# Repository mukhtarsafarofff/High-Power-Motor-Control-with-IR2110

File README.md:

(ENG) The IR2110 is a popular h-bridge half driver. It is designed to drive high voltage MOSFET and IGBT circuits. It does this without the use of p-channel MOSFETs or photovoltaic opto-couplers. The circuit generates HIGH side MOSFET gate voltage from a diode, bootstrap capacitor combination. The IR2110 is an 14-pin DIP IC and I used 2 for a complete h-bridge. The schematic to each half is identical. I used the 15V MOSFET/IGBT gate voltage with a 5-volt regular to supply the digital voltage (VDD) of 5V. The motor power supply is separate and is limited by the MOSFETs used and motor voltage up to 500-volts.  IR2110 illustration :
1) Pin 9 or VDD is the digital logic positive voltage range 3-15V. This enables the use of CMOS or LS TTL logic.
2) The VDD voltage depends on the type of logic connected to the inputs. I used a 5V Arduino so I connected 5V from a voltage regulator.
3) If using 3V logic such as Raspberry Pi GPIO connect to 3V. If using CMOS logic at say 12V connect VDD to 12V.
4) Pin 10 or HIN controls the output on pin 7 labeled HO that controls the HIGH side MOSFET. This input must be pulse-width-modulated as explained below.
5) Pin 12 or LIN controls the LOW side MOSFET connected to pin 1 LO. A HIGH outputs 10-15V on pin 1 turning on the LOW side MOSFET.
6) Pin 11 or SD will disable all outputs when HIGH. This is mostly connected to digital ground.
7) Pins 10, 11, and 12 all have Schmitt trigger inputs and internal pull down resistors.
8) Pin 13 or VSS is the digital power supply negative ground. This is often connected to motor supply HV voltage ground COM or pin 2.

Now comes the tricky part the output. The IR2110 uses to "bootstrap" capacitor to supply the gate turn on voltage for MOSFET Q1. MOSFETs Q1 and Q2 are connected in a "totem pole" configuration. Pin 7 supplies the gate drive voltage for HIGH side MOSFET Q1. Pin 1 supplies the gate drive voltage for LOW MOSFET Q2. Notice the internal "totem pole" outputs from LO and HO within the IR2110. VCC pin 3 is 10-15V gate drive voltage. Each have internal under voltage (UV) detectors. When the gate voltage drops below ~8.5V outputs are turned off. Capacitor Cb is charged through a diode from VCC to 15V. Internal transistor "A" will switch the capacitor voltage to gate Q1. Cb can no longer charge from VCC until Q1 is turned off. It is the charge-discharge of Cb connected across Q1 that keeps Q1 turned on. RL represents the load (motor for example) and the LOW side MOSFET turned on at the other half of the h-bridge. Capacitor Cb in my circuit is a 0.22uF or 220n. It is charged to 15V through diode D1. In my case I used a 1N4007. For high speed switching a UF4007 high speed diode must be used. D1 also serves to block the motor drive voltage from 15V VCC. The capacitor charges to 15V across VB and VS when Q1 is off. VS is connected to Q1 source connection. When a HIGH is input to HIN the voltage at VB is switched to pin HO turning on Q1. Once Q1 is turned on the motor voltage appears at Q1 source preventing any further charging of Cb. Cb will discharge the rate related to MOSFET leakage, etc. Most internet sites connect a 1K resistor across Q1 gate-source, I removed it. They also connected a 22uF electrolytic across Cb I removed that. They also failed to bypass VCC so I added 22uF capacitor to ground. I removed a 22uF bypass capacitor across VDD as not needed. Diode D2 was a 1N4007 in the test circuit. I used a 1N4148 high speed diode in the final circuit. MOSFETs tested: IRFZ40 - VDS = 60V; ID = 36A and IRFZ44N - VDS = 55V; ID = 49A. The following from IR application note AN978-b. VDD is 3-15V, the output stage is implemented either with two N-Channel MOSFETs in totem pole configuration. Each IR2110 MOSFET can sink or source gate currents up to 2A, depending on the MGD. MGD stands for MOS-gate-driver. To quote in regards to VB, VS, and HO: The gate charge for the high side MOSFET is provided by the bootstrap capacitor which is charged by the 15V supply through the bootstrap diode during the time when the device is off. The use of pulses greatly reduces the power dissipation associated with the level translation. The pulse discriminator filters the set/reset pulses from fast dv/dt transients appearing on the VS node so that switching rates as high as 50V/ns in the power devices will not adversely affect the operation of the MGD. This channel has its own undervoltage lockout ( on some MGDs) which blocks the gate drive if the voltage between VB and VS, i.e., the voltage across the upper totem pole is below its limits (typically 8.7/8.3V). The operation of the UV lockout differs from the one on VCC in one detail: the first pulse after the UV lockout has released the channel changes the state of the output. The high voltage level translator circuit is designed to function properly even when the VS node swings below the COM pin by a voltage indicated in the data sheet, typically 5 V. The following in my view is nonsense. I used a single 15V supply for VCC and the motor supply voltage. 12V should also work. It worked just fine with my h-bridge. Gate voltage must be 10-15V higher than the drain voltage. Being a high side switch, such gate voltage would have to be higher than the rail voltage, which is frequently the highest voltage available in the system. Code is here :

#define INAHI 5 // pwm input A HI MOSFET
#define INBHI 6 // pwm input B HI MOSFET
#define INALO 7 // input A LO MOSFET 
#define INBLO 8 // input B LO MOSFET

#define POT 0

#define SW1 2
#define SW2 3

int val;

void setup() {
  pinMode(INAHI, OUTPUT);
  pinMode(INBHI, OUTPUT);
  pinMode(INALO, OUTPUT);
  pinMode(INBLO, OUTPUT);

  digitalWrite(INAHI, LOW);
  digitalWrite(INBHI, LOW);
  digitalWrite(INALO, LOW);
  digitalWrite(INBLO, LOW);

  pinMode(SW1, INPUT);
  pinMode(SW2, INPUT);

  pinMode(SW1, INPUT_PULLUP);
  pinMode(SW2, INPUT_PULLUP);
}

void loop() {

  analogWrite(INAHI, 0);
  analogWrite(INBHI, 0);
  
  // INAHI HIGH and INBLO HIGH
  // INALO LOW and INBHI LOW
  while (!digitalRead(SW1))   {
    digitalWrite(INALO, LOW);
    digitalWrite(INBHI, LOW);
    val = analogRead(POT)/ 4 ;
    analogWrite(INAHI, val);
    digitalWrite(INBLO, HIGH); 
  }

  // INAHI LOW and INBLO LOW
  // INALO HIGH and INBHI HIGH
  while (!digitalRead(SW2))   {
  digitalWrite(INAHI, LOW);
  digitalWrite(INBLO, LOW);
  val = analogRead(POT)/ 4;
  analogWrite(INBHI, val);
  digitalWrite(INALO, HIGH); 
  }

} // end loop

(DEU)  Der IR2110 ist ein beliebter Halbbrückentreiber. Er ist dafür ausgelegt, Hochspannungs-MOSFET- und IGBT-Schaltungen zu steuern. Dies geschieht ohne die Verwendung von P-Kanal-MOSFETs oder photovoltaischen Optokopplern. Die Schaltung erzeugt die Gate-Spannung für den HIGH-Side-MOSFET aus einer Kombination von Diode und Bootstrap-Kondensator. Der IR2110 ist ein 14-poliges DIP-IC, und ich habe zwei davon für eine vollständige H-Brücke verwendet. Der Schaltplan für jede Hälfte ist identisch. Ich habe die 15V MOSFET/IGBT-Gate-Spannung mit einem 5-Volt-Regler verwendet, um die digitale Spannung (VDD) von 5V zu liefern. Die Motorstromversorgung ist separat und wird durch die verwendeten MOSFETs und die Motorspannung bis zu 500 Volt begrenzt. Illustration des IR2110: 
1) Pin 9 oder VDD ist die positive Logikspannung im Bereich von 3-15V. Dies ermöglicht die Verwendung von CMOS- oder LS-TTL-Logik.
2) Die VDD-Spannung hängt von der Art der Logik ab, die mit den Eingängen verbunden ist. Ich habe einen 5V-Arduino verwendet, daher habe ich 5V von einem Spannungsregler angeschlossen. Wenn Sie 3V-Logik wie Raspberry Pi GPIO verwenden, schließen Sie VDD an 3V an.
3) Wenn Sie CMOS-Logik mit beispielsweise 12V verwenden, schließen Sie VDD an 12V an.
4) Pin 10 oder HIN steuert den Ausgang an Pin 7, bezeichnet als HO, der den HIGH-Side-MOSFET steuert. Dieser Eingang muss wie unten erläutert pulsweitenmoduliert werden.
5) Pin 12 oder LIN steuert den LOW-Side-MOSFET, der an Pin 1 LO angeschlossen ist. Ein HIGH gibt 10-15V an Pin 1 aus und schaltet den LOW-Side-MOSFET ein.
6) Pin 11 oder SD deaktiviert alle Ausgänge, wenn er auf HIGH gesetzt ist. Dieser ist meistens mit der digitalen Masse verbunden.
7) Pins 10, 11 und 12 haben alle Schmitt-Trigger-Eingänge und interne Pull-Down-Widerstände.
8) Pin 13 oder VSS ist die negative Masse der digitalen Stromversorgung. Diese ist oft mit der Masse der Motorversorgung (HV) verbunden, COM oder Pin 2.
9) Pins 8 und 14 sind nicht verbunden.
Nun kommt der knifflige Teil: der Ausgang. Der IR2110 verwendet einen "Bootstrap"-Kondensator, um die Einschaltspannung für das Gate des MOSFET Q1 bereitzustellen. Die MOSFETs Q1 und Q2 sind in einer "Totem-Pole"-Konfiguration verbunden. Pin 7 liefert die Gate-Ansteuerspannung für den HIGH-Side-MOSFET Q1. Pin 1 liefert die Gate-Ansteuerspannung für den LOW-Side-MOSFET Q2. Beachten Sie die internen "Totem-Pole"-Ausgänge von LO und HO innerhalb des IR2110. Der VCC-Pin 3 ist eine Gate-Ansteuerspannung von 10-15V. Jeder hat interne Unterspannung (UV)-Detektoren. Wenn die Gate-Spannung unter etwa 8,5V fällt, werden die Ausgänge abgeschaltet. Der Kondensator Cb wird über eine Diode von VCC auf 15V aufgeladen. Der interne Transistor "A" schaltet die Kondensatorspannung zum Gate von Q1. Cb kann sich nicht mehr von VCC aufladen, bis Q1 ausgeschaltet ist. Es ist das Lade-Entlade-Verhalten von Cb, der über Q1 verbunden ist, das Q1 eingeschaltet hält. RL stellt die Last dar (zum Beispiel einen Motor), und der LOW-Side-MOSFET ist in der anderen Hälfte der H-Brücke eingeschaltet. Der Kondensator Cb in meiner Schaltung ist 0,22 µF oder 220 nF. Er wird über die Diode D1 auf 15V aufgeladen. In meinem Fall habe ich eine 1N4007 verwendet. Für schnelles Schalten muss eine UF4007 Hochgeschwindigkeitsdiode verwendet werden. D1 dient auch dazu, die Motortreiberspannung von der 15V-VCC zu blockieren. Der Kondensator lädt sich auf 15V über VB und VS auf, wenn Q1 ausgeschaltet ist . VS ist mit dem Source-Anschluss von Q1 verbunden. Wenn ein HIGH-Signal an HIN angelegt wird, wird die Spannung an VB auf den Pin HO geschaltet und schaltet Q1 ein. Sobald Q1 eingeschaltet ist, erscheint die Motorspannung am Source-Anschluss von Q1 und verhindert eine weitere Aufladung von Cb. Cb entlädt sich mit einer Rate, die von der Leckstrom des MOSFETs und anderen Faktoren abhängt. Die meisten Internetseiten verbinden einen 1K-Widerstand zwischen Gate und Source von Q1, den habe ich entfernt. Sie haben auch einen 22uF-Elektrolytkondensator parallel zu Cb geschaltet, den habe ich ebenfalls entfernt. Sie haben VCC nicht gebypasst, also habe ich einen 22uF-Kondensator zur Erdung hinzugefügt. . Ich habe einen 22uF-Bypasskondensator parallel zu VDD entfernt, da er nicht benötigt wird. Diode D2 war im Testschaltkreis eine 1N4007. Ich habe in der endgültigen Schaltung eine 1N4148-Hochgeschwindigkeitsdiode verwendet. Getestete MOSFETs: IRFZ40 - VDS = 60V; ID = 36A und IRFZ44N - VDS = 55V; ID = 49A. Das Folgende stammt aus der IR-Anwendungsnote AN978-b. VDD beträgt 3-15V, die Ausgangsstufe wird entweder mit zwei N-Kanal-MOSFETs in Totem-Pole-Konfiguration implementiert. Jeder IR2110 MOSFET kann Gate-Ströme bis zu 2A aufnehmen oder abgeben, abhängig vom MGD. MGD steht für MOS-Gate-Treiber. Zitat zu VB, VS und HO: Die Gate-Ladung für den High-Side-MOSFET wird durch den Bootstrap-Kondensator bereitgestellt, der durch die 15V-Versorgung über die Bootstrap-Diode während der Zeit aufgeladen wird, in der das Gerät ausgeschaltet ist. Die Verwendung von Impulsen reduziert die Leistungsabgabe, die mit der Pegelübersetzung verbunden ist, erheblich. Der Impulsdiskriminator filtert die Set/Reset-Impulse von schnellen dv/dt-Übergängen, die am VS-Knoten auftreten, sodass Schaltgeschwindigkeiten von bis zu 50V/ns in den Leistungsbauteilen die Funktion des MGD nicht negativ beeinflussen. Dieser Kanal hat eine eigene Unterspannungssperre (bei einigen MGDs), die den Gate-Antrieb blockiert, wenn die Spannung zwischen VB und VS, d.h. die Spannung über dem oberen Totem-Pole, unterhalb ihrer Grenzwerte liegt (typischerweise 8,7/8,3V). Die Funktionsweise der UV-Sperre unterscheidet sich in einem Detail von derjenigen bei VCC: : Der erste Impuls nach dem Freigeben der UV-Sperre ändert den Zustand des Ausgangs. Die Hochspannungs-Pegelübersetzungsschaltung ist so ausgelegt, dass sie ordnungsgemäß funktioniert, selbst wenn der VS-Knoten unterhalb des COM-Pins um eine im Datenblatt angegebene Spannung, typischerweise 5V, schwingt. Das Folgende halte ich für Unsinn.  Ich habe eine einzige 15V-Versorgung für VCC und die Motorspannung verwendet.  12V sollte auch funktionieren. Es funktionierte einwandfrei mit meiner H-Brücke. Die Gate-Spannung muss 10-15V höher als die Drain-Spannung sein.  Als High-Side-Schalter muss eine solche Gate-Spannung höher als die Rail-Spannung sein, die häufig die höchste im System verfügbare Spannung ist.

#define INAHI 5
// pwm input A HI MOSFET
#define INBHI 6
// pwm input B HI MOSFET #define INALO 7
// input A LO MOSFET #define INBLO 8
// input B LO MOSFET

#define POT 0

#define SW1 2 #define SW2 3

int val;

void setup() { 
pinMode(INAHI, OUTPUT); 
pinMode(INBHI, OUTPUT);
pinMode(INALO, OUTPUT);
pinMode(INBLO, OUTPUT);

digitalWrite(INAHI, LOW); 
digitalWrite(INBHI, LOW); 
digitalWrite(INALO, LOW); 
digitalWrite(INBLO, LOW);

pinMode(SW1, INPUT); 
pinMode(SW2, INPUT);

pinMode(SW1, INPUT_PULLUP);
pinMode(SW2, INPUT_PULLUP); 
}

void loop() {

analogWrite(INAHI, 0);
analogWrite(INBHI, 0);

// INAHI HIGH and INBLO HIGH 
// INALO LOW and INBHI LOW 
while (!digitalRead(SW1)) {
digitalWrite(INALO, LOW);
digitalWrite(INBHI, LOW); 
val = analogRead(POT)/4;
analogWrite(INAHI, val); 
digitalWrite(INBLO, HIGH); }

// INAHI LOW and INBLO LOW 
//INALO HIGH and INBHI HIGH 
while (!digitalRead(SW2)) 
{ digitalWrite(INAHI, LOW); 
digitalWrite(INBLO, LOW); 
val = analogRead(POT)/ 4;
analogWrite(INBHI, val); 
digitalWrite(INALO, HIGH); }

} 
// end loop

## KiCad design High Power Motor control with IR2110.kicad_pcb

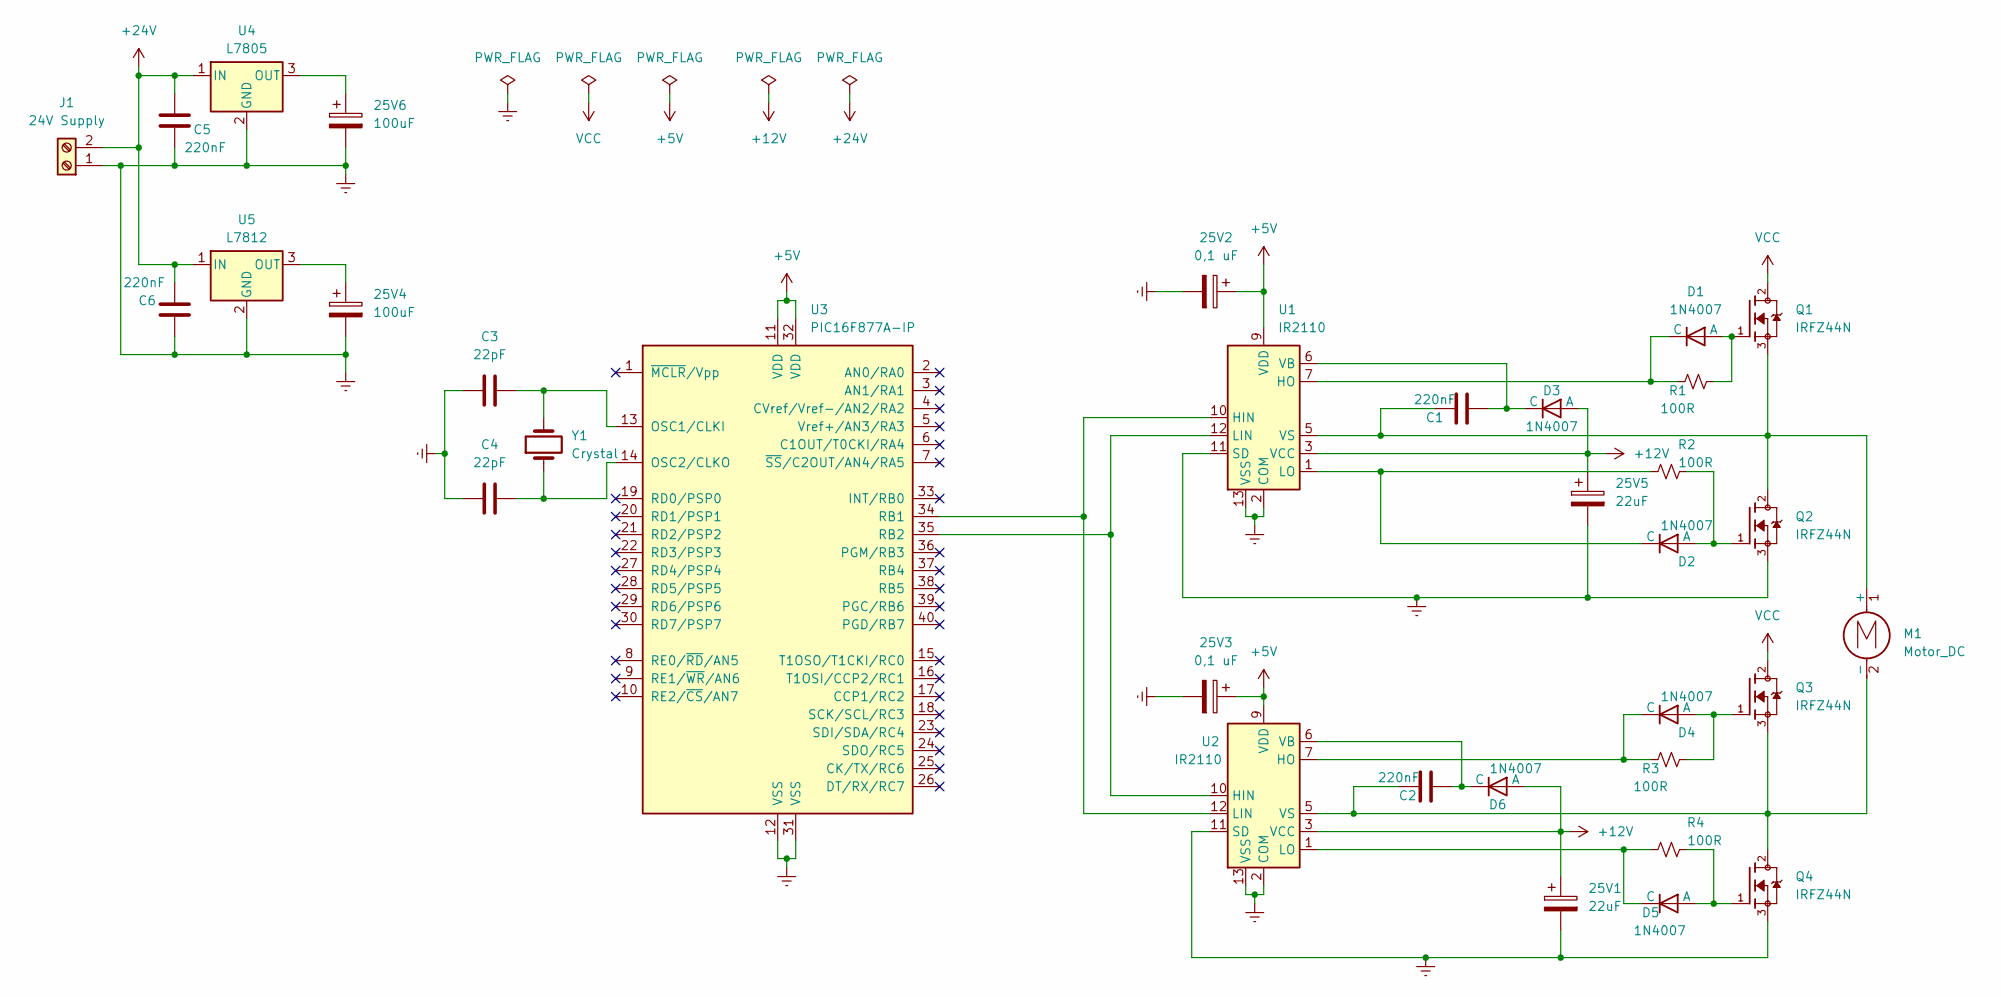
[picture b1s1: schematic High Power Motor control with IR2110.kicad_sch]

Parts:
25V1, 25V5: 22uF; CP_Radial_D16.0mm_P7.50mm
25V2, 25V3: 0,1 uF; CP_Radial_D10.0mm_P7.50mm
25V4, 25V6: 100uF; CP_Radial_D18.0mm_P7.50mm
C1, C2, C5, C6: 220nF; C_Disc_D12.5mm_W5.0mm_P7.50mm
C3, C4: 22pF; C_Disc_D12.5mm_W5.0mm_P7.50mm
D1, D2, D3, D4, D5, D6: 1N4007; D_5W_P12.70mm_Horizontal
J1: 24V Supply; TerminalBlock_Phoenix_MKDS-1,5-2-5.08_1x02_P5.08mm_Horizont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
M1: Motor_DC; TerminalBlock_Phoenix_MKDS-1,5-2-5.08_1x02_P5.08mm_Horizont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
Q1, Q2, Q3, Q4: IRFZ44N; TO254P1016X419X2286-3; PARTREV 09/21/10
R1, R2, R3, R4: 100R; R_Axial_DIN0614_L14.3mm_D5.7mm_P15.24mm_Horizontal
U1, U2: IR2110; DIP-14_W7.62mm
U3: PIC16F877A-IP; DIP-40_W15.24mm
U4: L7805; TO254P1016X419X2286-3
U5: L7812; TO254P1016X419X2286-3
Y1: Crystal; Crystal_HC52-6mm_Vertical

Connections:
+5V: 25V2.1, 25V3.1, U1.9 (VDD), U2.9 (VDD), U3.11 (VDD), U3.32 (VDD)
+12V: 25V1.1, 25V5.1, D3.1 (A), D6.1 (A), U1.3 (VCC), U2.3 (VCC)
Earth: 25V1.2, 25V2.2, 25V3.2, 25V4.2, 25V5.2, 25V6.2, C3.1, C4.1, C5.2, C6.1, J1.1, Q2.3, Q4.3, U1.2 (COM), U1.11 (SD), U1.13 (VSS), U2.2 (COM), U2.11 (SD), U2.13 (VSS), U3.12 (VSS), U3.31 (VSS), U4.2 (GND), U5.2 (GND)
unnamed: D1.1 (A), Q1.1, R1.1
unnamed: D1.2 (C), R1.2, U1.7 (HO)
unnamed: D2.1 (A), Q2.1, R2.1
unnamed: D2.2 (C), R2.2, U1.1 (LO)
unnamed: C1.2, D3.2 (C), U1.6 (VB)
unnamed: D4.1 (A), Q3.1, R3.1
unnamed: D4.2 (C), R3.2, U2.7 (HO)
unnamed: D5.1 (A), Q4.1, R4.1
unnamed: D5.2 (C), R4.2, U2.1 (LO)
unnamed: C2.2, D6.2 (C), U2.6 (VB)
unnamed: C5.1, C6.2, J1.2, U4.1 (IN), U5.1 (IN)
unnamed: C1.1, M1.1 (+), Q1.3, Q2.2, U1.5 (VS)
unnamed: C2.1, M1.2 (-), Q3.3, Q4.2, U2.5 (VS)
unnamed: U1.10 (HIN), U2.12 (LIN), U3.34 (RB1)
unnamed: U1.12 (LIN), U2.10 (HIN), U3.35 (RB2)
unnamed: C3.2, U3.13 (OSC1/CLKI), Y1.2
unnamed: C4.2, U3.14 (OSC2/CLKO), Y1.1
unnamed: 25V6.1, U4.3 (OUT)
unnamed: 25V4.1, U5.3 (OUT)
VCC: Q1.2, Q3.2

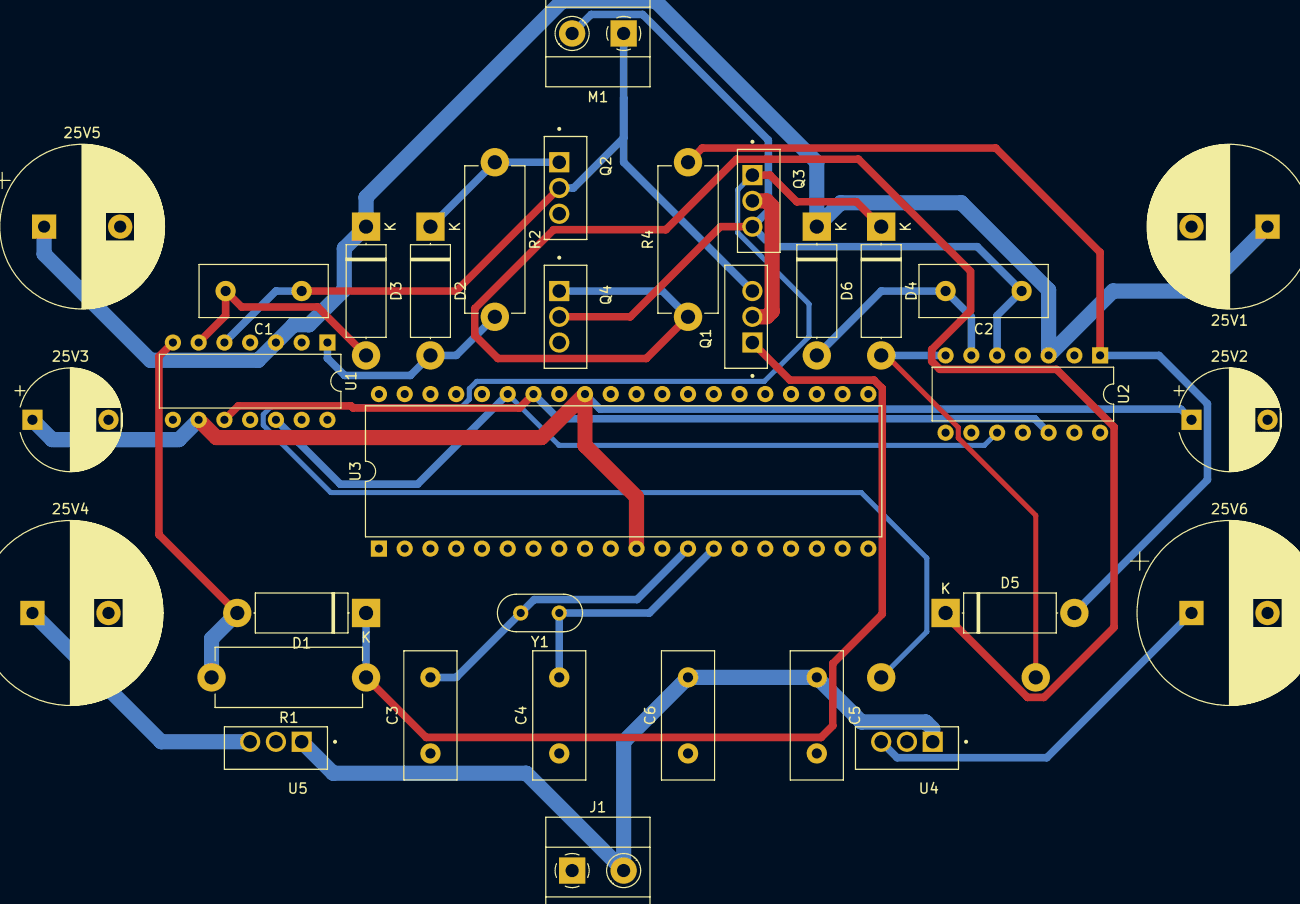
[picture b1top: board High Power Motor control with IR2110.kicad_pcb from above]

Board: 2 copper layers, 34 parts (1 on the bottom side), 23 nets.

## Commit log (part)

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2024-05-23 High Power Motor Control Module is accomplished
